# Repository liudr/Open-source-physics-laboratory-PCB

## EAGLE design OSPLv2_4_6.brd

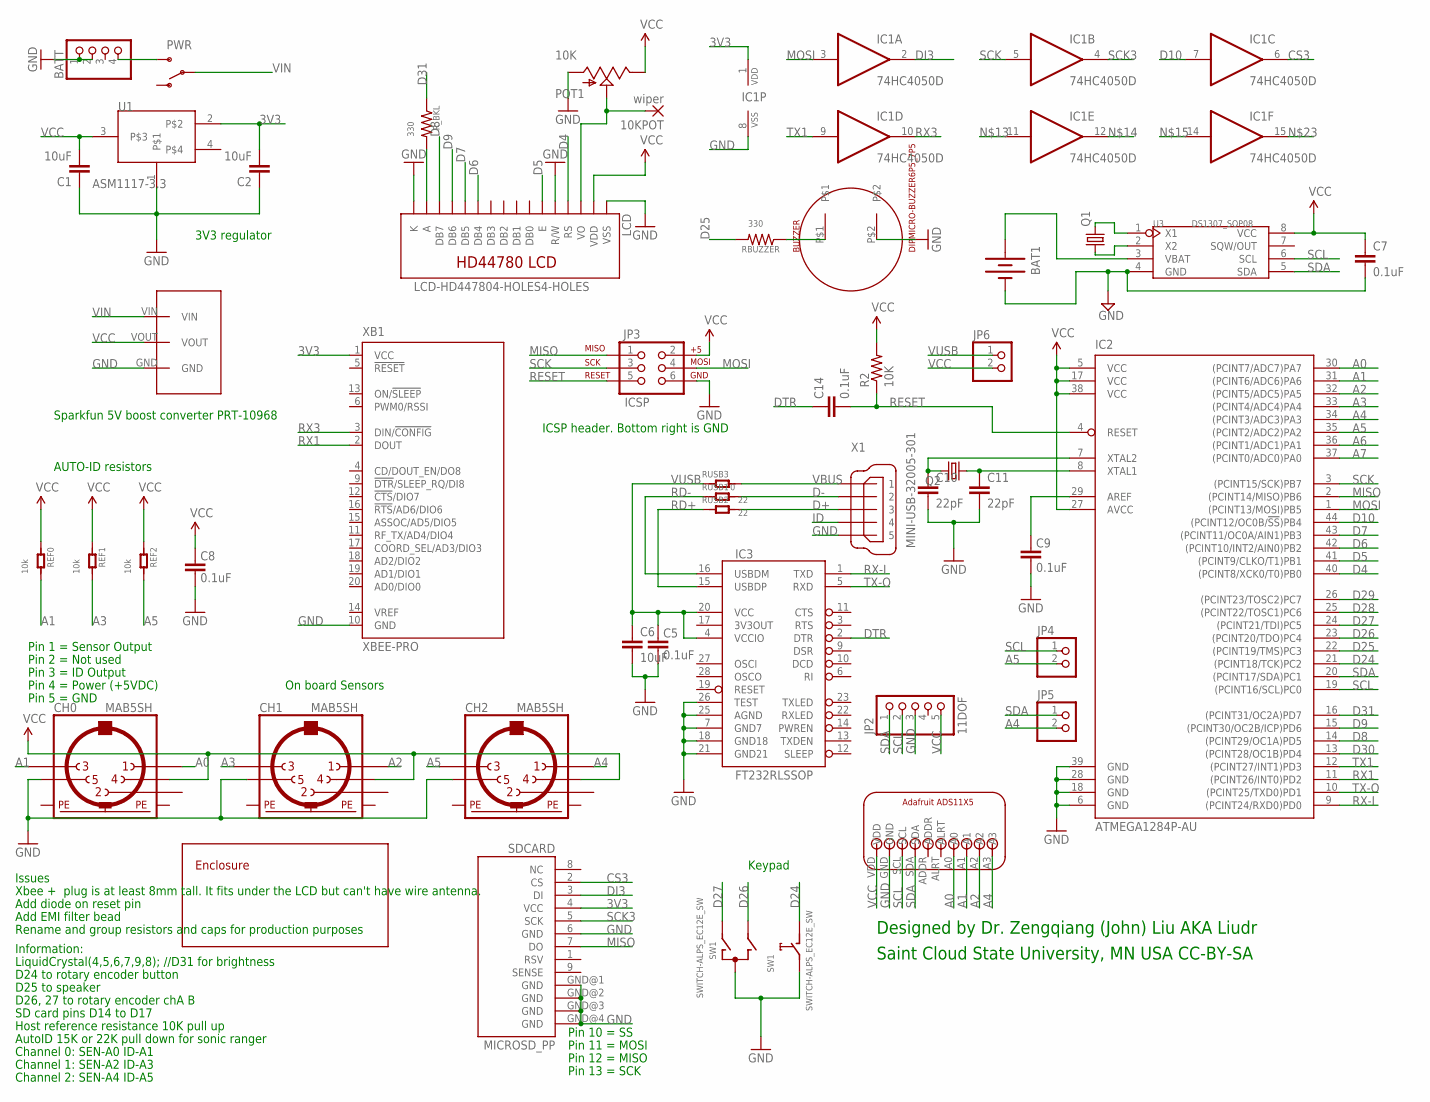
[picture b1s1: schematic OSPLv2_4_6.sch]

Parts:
10KPOT: wiper; 1,6/0,9
BAT1: BATTERYHARWIN12MMHOLDER; HARWIN12MMHOLDER
BATT: PINHD-1X40; 1X04
BUZZER: DIPMICRO-BUZZER6P5_7P5; BUZZER-6P5-7P5
C1, C2, C6: 10uF; 0603-CAP
C5, C7, C8, C9, C14: 0.1uF; 0603-CAP
C10, C11: 22pF; 0603-CAP
CH0, CH1, CH2: MAB5SH
IC1: 74HC4050D; SO16
IC2: ATMEGA1284P-AU; TQFP44
IC3: FT232RLSSOP; SSOP28DB
JP2: 11DOF; 1X05
JP3: ICSP; 2X3
JP4, JP5, JP6: PINHD-1X2SMALL-PADS; 1X02-BIG
LCD: LCD-HD447804-HOLES4-HOLES; LCD-16X2-0HOLES-NO-FRAME
POT1: 10K; 3362U
PWR: SWITCH-SPSTPTH; SWITCH-SPDT
Q1: CRYSTALTC26H; TC26H
Q2: CRYSTALHC49UP; HC49UP
R2: 10K; 0603-RES
RBUZZER: 330; 0603-RES
REF0, REF1, REF2: 10k; R0603
RUSB1, RUSB2: 22; R0603
RUSB3: 0; R0603
R_BKL: 330; 0603-RES
SDCARD: MICROSD_PP
SPEDC-DC: DC-DCBOOSTSPE-DC-DCBOOSTSPE-DC-DC-BOOST; SPE-DC-DC-BOOST
SW1: SWITCH-ALPS_EC12E_SW; SWITCH-ALPS_ALPS_EC12E_SW
U1: ASM1117-3.3; SOT223
U3: DS1307_SOP08; SOP08
U$1: ENCLOSUREAG-54; BUSHING-AG-54
U$2: ADAFRUIT-ADCADS11X5ADS11X5; ADAFRUIT-ADC
X1: MINI-USB-32005-301; 32005-301
XB1: XBEE-PRO

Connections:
3V3: C2.2, IC1.1 (VDD), SDCARD.4 (VCC), U1.2, XB1.1 (VCC)
A0: CH0.1, IC2.30 ((PCINT7/ADC7)PA7), U$2.A0
A1: CH0.3, IC2.31 ((PCINT6/ADC6)PA6), REF0.2, U$2.A1
A2: CH1.1, IC2.32 ((PCINT5/ADC5)PA5), U$2.A2
A3: CH1.3, IC2.33 ((PCINT4/ADC4)PA4), REF1.2
A4: CH2.1, IC2.34 ((PCINT3/ADC3)PA3), JP5.2, U$2.A3
A5: CH2.3, IC2.35 ((PCINT2/ADC2)PA2), JP4.2, REF2.2
A6: IC2.36 ((PCINT1/ADC1)PA1)
A7: IC2.37 ((PCINT0/ADC0)PA0)
AREF1: C9.2, IC2.29 (AREF)
CS3: IC1.6 (O), SDCARD.2 (CS)
D4: IC2.40 ((PCINT8/XCK0/T0)PB0), LCD.RS
D5: IC2.41 ((PCINT9/CLKO/T1)PB1), LCD.E
D6: IC2.42 ((PCINT10/INT2/AIN0)PB2), LCD.DB4
D7: IC2.43 ((PCINT11/OC0A/AIN1)PB3), LCD.DB5
D8: IC2.14 ((PCINT29/OC1A)PD5), LCD.DB7
D9: IC2.15 ((PCINT30/OC2B/ICP)PD6), LCD.DB6
D10: IC1.7 (I), IC2.44 ((PCINT12/OC0B/!SS!)PB4)
D24: IC2.21 ((PCINT18/TCK)PC2), SW1.D (1)
D25: IC2.22 ((PCINT19/TMS)PC3), RBUZZER.2
D26: IC2.23 ((PCINT20/TDO)PC4), SW1.B
D27: IC2.24 ((PCINT21/TDI)PC5), SW1.A
D28: IC2.25 ((PCINT22/TOSC1)PC6)
D29: IC2.26 ((PCINT23/TOSC2)PC7)
D30: IC2.13 ((PCINT28/OC1B)PD4)
D31: IC2.16 ((PCINT31/OC2A)PD7), R_BKL.1
D+: RUSB2.2, X1.3
D-: RUSB1.2, X1.2
DI3: IC1.2 (O), SDCARD.3 (DI)
DTR: C14.1, IC3.2 (DTR)
GND: BAT1.PADGND (-), BATT.1, BATT.2, BUZZER.P$2, C1.1, C2.1, C5.1, C6.2, C7.2, C8.1, C9.1, C10.2, C11.2, CH0.5, CH1.5, CH2.5, IC1.8 (VSS), IC2.6 (GND), IC2.18 (GND), IC2.28 (GND), IC2.39 (GND), IC3.7 (GND7), IC3.18 (GND18), IC3.21 (GND21), IC3.25 (AGND), IC3.26 (TEST), JP2.3, JP3.6, LCD.K, LCD.R/W, LCD.VSS, POT1.P$3 (A), SDCARD.6 (GND), SDCARD.GND@1 (GND), SDCARD.GND@2 (GND), SDCARD.GND@3 (GND), SDCARD.GND@4 (GND), SPEDC-DC.GND, SW1.C, SW1.E (2), U1.1, U3.4 (GND), U$2.GND, X1.5, XB1.10 (GND)
ID: X1.4
MISO: IC2.2 ((PCINT14/MISO)PB6), JP3.1, SDCARD.7 (DO)
MOSI: IC1.3 (I), IC2.1 ((PCINT13/MOSI)PB5), JP3.4
unnamed: C11.1, IC2.8 (XTAL1), Q2.1
unnamed: C10.1, IC2.7 (XTAL2), Q2.2
unnamed: Q1.2, U3.1 (X1)
unnamed: LCD.A, R_BKL.2
unnamed: BATT.4, PWR.3 (S)
unnamed: BAT1.PAD3V3 (+), U3.3 (VBAT)
unnamed: 10KPOT.1, LCD.VO, POT1.P$2 (S)
unnamed: Q1.1, U3.2 (X2)
unnamed: BUZZER.P$1, RBUZZER.1
PE: CH0.PE, CH0.PE@ (PE), CH1.PE, CH1.PE@ (PE), CH2.PE, CH2.PE@ (PE)
RD+: IC3.15 (USBDP), RUSB2.1
RD-: IC3.16 (USBDM), RUSB1.1
RESET: C14.2, IC2.4 (RESET), JP3.5, R2.1
RX1: IC2.11 ((PCINT26/INT0)PD2), XB1.2 (DOUT)
RX3: IC1.10 (O), XB1.3 (DIN/!CONFIG)
RX-I: IC2.9 ((PCINT24/RXD0)PD0), IC3.1 (TXD)
SCK: IC1.5 (I), IC2.3 ((PCINT15/SCK)PB7), JP3.3
SCK3: IC1.4 (O), SDCARD.5 (SCK)
SCL: IC2.19 ((PCINT16/SCL)PC0), JP2.2, JP4.1, U3.6 (SCL), U$2.SCL
SDA: IC2.20 ((PCINT17/SDA)PC1), JP2.1, JP5.1, U3.5 (SDA), U$2.SDA
TX1: IC1.9 (I), IC2.12 ((PCINT27/INT1)PD3)
TX-O: IC2.10 ((PCINT25/TXD0)PD1), IC3.5 (RXD)
VBUS: RUSB3.2, X1.1
VCC: C1.2, C7.1, C8.2, CH0.4, CH1.4, CH2.4, IC2.5 (VCC), IC2.17 (VCC), IC2.27 (AVCC), IC2.38 (VCC), JP2.5, JP3.2, JP6.2, LCD.VDD, POT1.P$1 (E), R2.2, REF0.1, REF1.1, REF2.1, SPEDC-DC.VOUT, U1.3, U3.8 (VCC), U$2.VDD
VIN: PWR.2, SPEDC-DC.VIN
VUSB: C5.2, C6.1, IC3.4 (VCCIO), IC3.20 (VCC), JP6.1, RUSB3.1

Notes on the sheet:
On board Sensors
Keypad
Channel 0: SEN-A0 ID-A1
Channel 1: SEN-A2 ID-A3
Channel 2: SEN-A4 ID-A5
D25 to speaker
Host reference resistance 10K pull up
AutoID 15K or 22K pull down for sonic ranger
Issues
LiquidCrystal(4,5,6,7,9,8); //D31 for brightness
Pin 1 = Sensor Output
Pin 2 = Not used
Pin 3 = ID Output
Pin 4 = Power (+5VDC)
Pin 5 = GND
Information:
SD card pins D14 to D17
3V3 regulator
AUTO-ID resistors
Pin 13 = SCK
Pin 12 = MISO
Pin 11 = MOSI
Pin 10 = SS
D24 to rotary encoder button
Sparkfun 5V boost converter PRT-10968
Add diode on reset pin
ICSP header. Bottom right is GND
Xbee + plug is at least 8mm tall. It fits under the LCD but can't have wire antenna.
D26, 27 to rotary encoder chA B
Add EMI filter bead
Designed by Dr. Zengqiang (John) Liu AKA Liudr
Saint Cloud State University, MN USA CC-BY-SA
Rename and group resistors and caps for production purposes

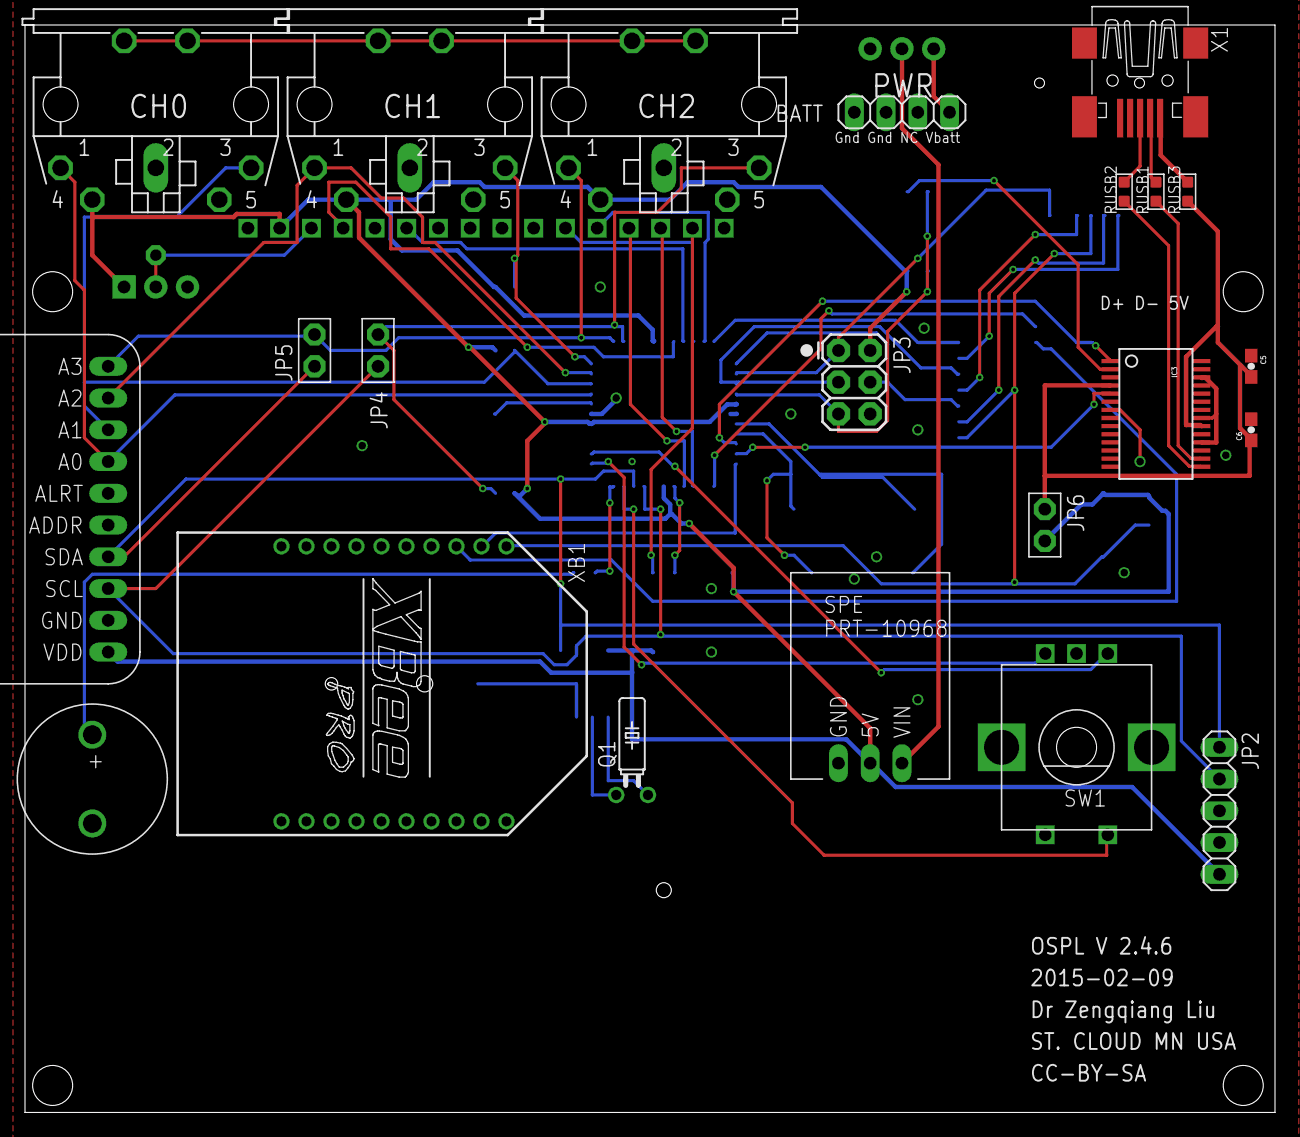
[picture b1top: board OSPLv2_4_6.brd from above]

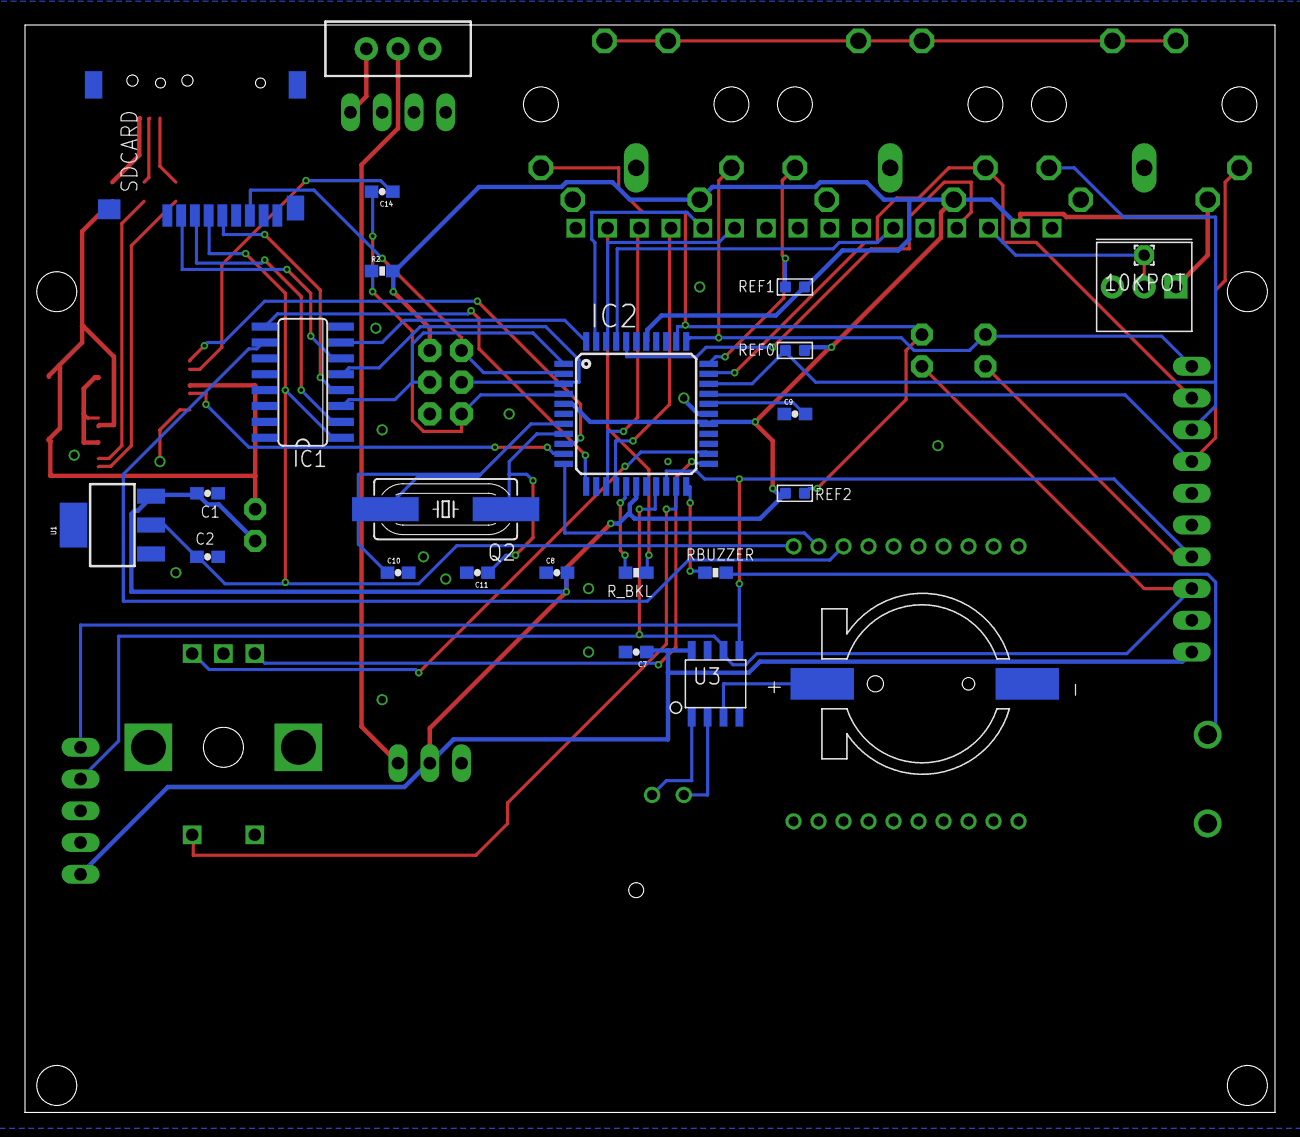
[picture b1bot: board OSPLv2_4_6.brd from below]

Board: 2 copper layers, 100.0 x 87.0 mm, 48 parts (24 on the bottom side), 54 nets.

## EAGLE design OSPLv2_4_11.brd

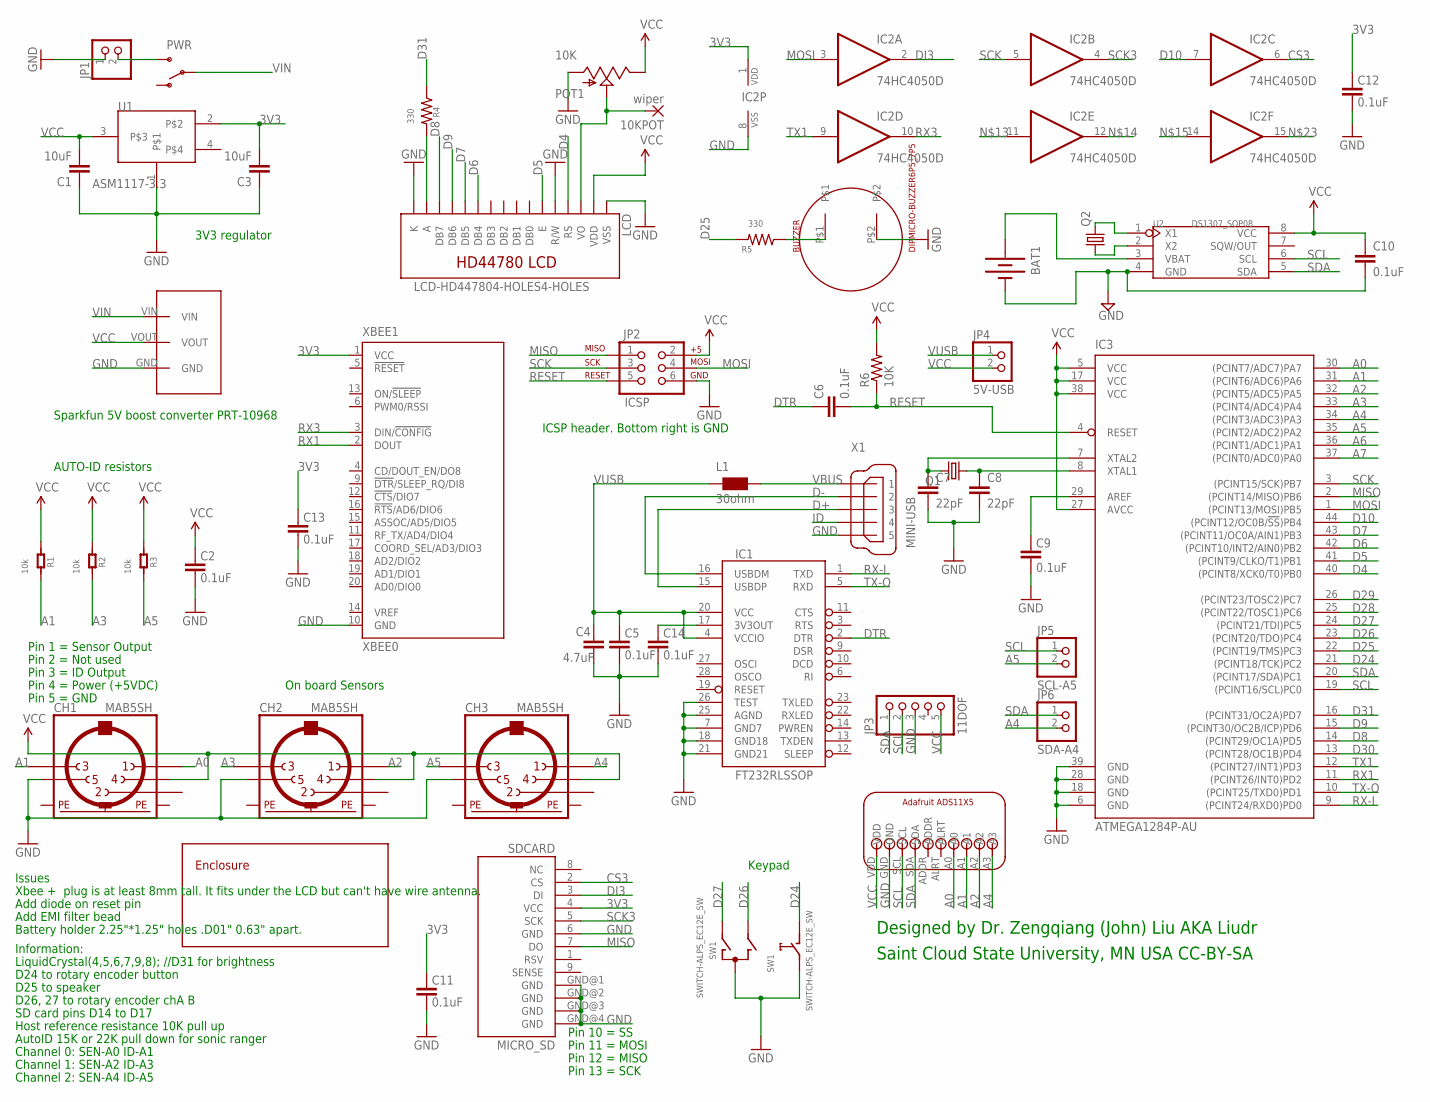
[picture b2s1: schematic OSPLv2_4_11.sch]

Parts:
10KPOT: wiper; 1,6/0,9
BAT1: BATTERYHARWIN12MMHOLDER; HARWIN12MMHOLDER
BUZZER: DIPMICRO-BUZZER6P5_7P5; BUZZER-6P5-7P5
C1, C3: 10uF; 0603-CAP
C2, C5, C6, C9, C10, C11, C12, C13, C14: 0.1uF; 0603-CAP
C4: 4.7uF; 0603-CAP
C7, C8: 22pF; 0603-CAP
CH1, CH2, CH3: MAB5SH
IC1: FT232RLSSOP; SSOP28DB
IC2: 74HC4050D; SO16
IC3: ATMEGA1284P-AU; TQFP44
JP1: PINHD-1X2SMALL-PADS; 1X02-BIG
JP2: ICSP; 2X3
JP3: 11DOF; 1X05
JP4: 5V-USB; 1X02-BIG
JP5: SCL-A5; 1X02-BIG
JP6: SDA-A4; 1X02-BIG
L1: 30ohm; 0805
LCD: LCD-HD447804-HOLES4-HOLES; LCD-16X2-0HOLES-NO-FRAME
POT1: 10K; 3362U
PWR: SWITCH-SPSTPTH; SWITCH-SPDT
Q1: CRYSTALHC49UP; HC49UP
Q2: CRYSTALTC26H; TC26H
R1, R2, R3: 10k; R0603
R4, R5: 330; 0603-RES
R6: 10K; 0603-RES
SDCARD: MICRO_SD; MICROSD_PP
SPEDC-DC: DC-DCBOOSTSPE-DC-DCBOOSTSPE-DC-DC-BOOST; SPE-DC-DC-BOOST
SW1: SWITCH-ALPS_EC12E_SW; SWITCH-ALPS_ALPS_EC12E_SW
U1: ASM1117-3.3; SOT223
U2: DS1307_SOP08; SOP08
U$1: ENCLOSUREAG-54; BUSHING-AG-54
U$2: ADAFRUIT-ADCADS11X5ADS11X5; ADAFRUIT-ADC
X1: MINI-USB; 32005-301
XBEE1: XBEE0; XBEE-PRO

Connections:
3V3: C3.2, C11.2, C12.2, C13.2, IC2.1 (VDD), SDCARD.4 (VCC), U1.2, XBEE1.1 (VCC)
A0: CH1.1, IC3.30 ((PCINT7/ADC7)PA7), U$2.A0
A1: CH1.3, IC3.31 ((PCINT6/ADC6)PA6), R1.2, U$2.A1
A2: CH2.1, IC3.32 ((PCINT5/ADC5)PA5), U$2.A2
A3: CH2.3, IC3.33 ((PCINT4/ADC4)PA4), R2.2
A4: CH3.1, IC3.34 ((PCINT3/ADC3)PA3), JP6.2, U$2.A3
A5: CH3.3, IC3.35 ((PCINT2/ADC2)PA2), JP5.2, R3.2
A6: IC3.36 ((PCINT1/ADC1)PA1)
A7: IC3.37 ((PCINT0/ADC0)PA0)
AREF1: C9.2, IC3.29 (AREF)
CS3: IC2.6 (O), SDCARD.2 (CS)
D4: IC3.40 ((PCINT8/XCK0/T0)PB0), LCD.RS
D5: IC3.41 ((PCINT9/CLKO/T1)PB1), LCD.E
D6: IC3.42 ((PCINT10/INT2/AIN0)PB2), LCD.DB4
D7: IC3.43 ((PCINT11/OC0A/AIN1)PB3), LCD.DB5
D8: IC3.14 ((PCINT29/OC1A)PD5), LCD.DB7
D9: IC3.15 ((PCINT30/OC2B/ICP)PD6), LCD.DB6
D10: IC2.7 (I), IC3.44 ((PCINT12/OC0B/!SS!)PB4)
D24: IC3.21 ((PCINT18/TCK)PC2), SW1.D (1)
D25: IC3.22 ((PCINT19/TMS)PC3), R5.2
D26: IC3.23 ((PCINT20/TDO)PC4), SW1.B
D27: IC3.24 ((PCINT21/TDI)PC5), SW1.A
D28: IC3.25 ((PCINT22/TOSC1)PC6)
D29: IC3.26 ((PCINT23/TOSC2)PC7)
D30: IC3.13 ((PCINT28/OC1B)PD4)
D31: IC3.16 ((PCINT31/OC2A)PD7), R4.1
D+: IC1.15 (USBDP), X1.3
D-: IC1.16 (USBDM), X1.2
DI3: IC2.2 (O), SDCARD.3 (DI)
DTR: C6.1, IC1.2 (DTR)
GND: BAT1.PADGND (-), BUZZER.P$2, C1.1, C2.1, C3.1, C4.2, C5.1, C7.2, C8.2, C9.1, C10.2, C11.1, C12.1, C13.1, C14.1, CH1.5, CH2.5, CH3.5, IC1.7 (GND7), IC1.18 (GND18), IC1.21 (GND21), IC1.25 (AGND), IC1.26 (TEST), IC2.8 (VSS), IC3.6 (GND), IC3.18 (GND), IC3.28 (GND), IC3.39 (GND), JP1.1, JP2.6, JP3.3, LCD.K, LCD.R/W, LCD.VSS, POT1.P$3 (A), SDCARD.6 (GND), SDCARD.GND@1 (GND), SDCARD.GND@2 (GND), SDCARD.GND@3 (GND), SDCARD.GND@4 (GND), SPEDC-DC.GND, SW1.C, SW1.E (2), U1.1, U2.4 (GND), U$2.GND, X1.5, XBEE1.10 (GND)
ID: X1.4
MISO: IC3.2 ((PCINT14/MISO)PB6), JP2.1, SDCARD.7 (DO)
MOSI: IC2.3 (I), IC3.1 ((PCINT13/MOSI)PB5), JP2.4
unnamed: C8.1, IC3.8 (XTAL1), Q1.1
unnamed: C7.1, IC3.7 (XTAL2), Q1.2
unnamed: Q2.2, U2.1 (X1)
unnamed: LCD.A, R4.2
unnamed: JP1.2, PWR.3 (S)
unnamed: BAT1.PAD3V3 (+), U2.3 (VBAT)
unnamed: 10KPOT.1, LCD.VO, POT1.P$2 (S)
unnamed: Q2.1, U2.2 (X2)
unnamed: C14.2, IC1.17 (3V3OUT)
unnamed: BUZZER.P$1, R5.1
PE: CH1.PE, CH1.PE@ (PE), CH2.PE, CH2.PE@ (PE), CH3.PE, CH3.PE@ (PE)
RESET: C6.2, IC3.4 (RESET), JP2.5, R6.1
RX1: IC3.11 ((PCINT26/INT0)PD2), XBEE1.2 (DOUT)
RX3: IC2.10 (O), XBEE1.3 (DIN/!CONFIG)
RX-I: IC1.1 (TXD), IC3.9 ((PCINT24/RXD0)PD0)
SCK: IC2.5 (I), IC3.3 ((PCINT15/SCK)PB7), JP2.3
SCK3: IC2.4 (O), SDCARD.5 (SCK)
SCL: IC3.19 ((PCINT16/SCL)PC0), JP3.2, JP5.1, U2.6 (SCL), U$2.SCL
SDA: IC3.20 ((PCINT17/SDA)PC1), JP3.1, JP6.1, U2.5 (SDA), U$2.SDA
TX1: IC2.9 (I), IC3.12 ((PCINT27/INT1)PD3)
TX-O: IC1.5 (RXD), IC3.10 ((PCINT25/TXD0)PD1)
VBUS: L1.2, X1.1
VCC: C1.2, C2.2, C10.1, CH1.4, CH2.4, CH3.4, IC3.5 (VCC), IC3.17 (VCC), IC3.27 (AVCC), IC3.38 (VCC), JP2.2, JP3.5, JP4.2, LCD.VDD, POT1.P$1 (E), R1.1, R2.1, R3.1, R6.2, SPEDC-DC.VOUT, U1.3, U2.8 (VCC), U$2.VDD
VIN: PWR.2, SPEDC-DC.VIN
VUSB: C4.1, C5.2, IC1.4 (VCCIO), IC1.20 (VCC), JP4.1, L1.1

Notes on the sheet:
On board Sensors
Keypad
Channel 0: SEN-A0 ID-A1
Channel 1: SEN-A2 ID-A3
Channel 2: SEN-A4 ID-A5
D25 to speaker
Host reference resistance 10K pull up
AutoID 15K or 22K pull down for sonic ranger
Issues
LiquidCrystal(4,5,6,7,9,8); //D31 for brightness
Pin 1 = Sensor Output
Pin 2 = Not used
Pin 3 = ID Output
Pin 4 = Power (+5VDC)
Pin 5 = GND
Information:
SD card pins D14 to D17
3V3 regulator
AUTO-ID resistors
Pin 13 = SCK
Pin 12 = MISO
Pin 11 = MOSI
Pin 10 = SS
D24 to rotary encoder button
Sparkfun 5V boost converter PRT-10968
Add diode on reset pin
ICSP header. Bottom right is GND
Xbee + plug is at least 8mm tall. It fits under the LCD but can't have wire antenna.
D26, 27 to rotary encoder chA B
Add EMI filter bead
Designed by Dr. Zengqiang (John) Liu AKA Liudr
Saint Cloud State University, MN USA CC-BY-SA
Battery holder 2.25"*1.25" holes .D01" 0.63" apart.

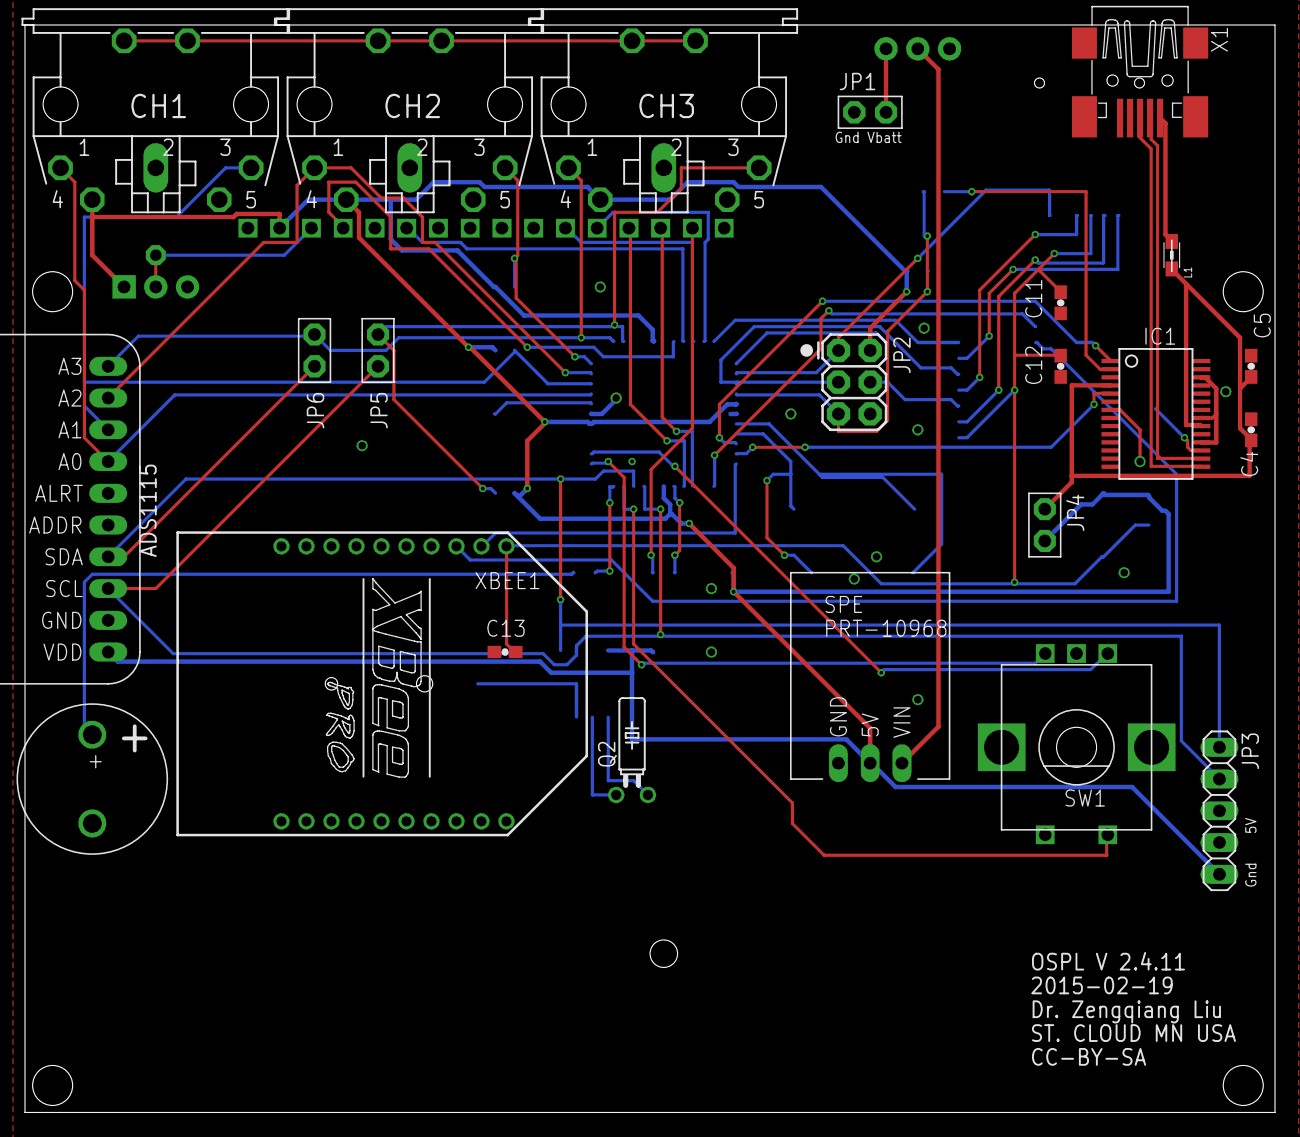
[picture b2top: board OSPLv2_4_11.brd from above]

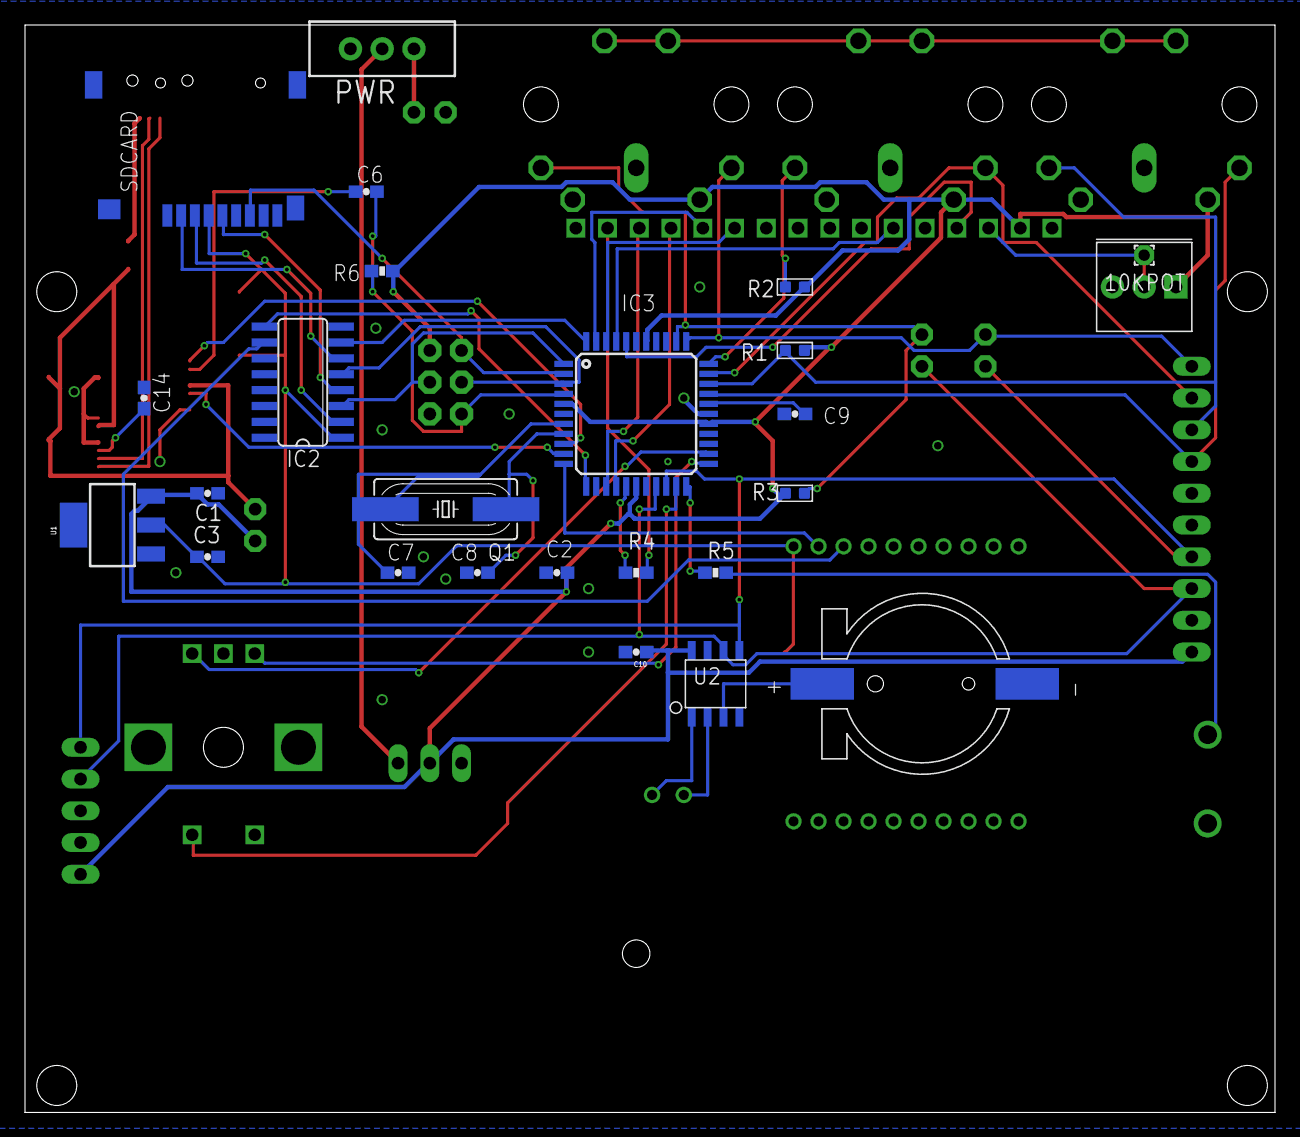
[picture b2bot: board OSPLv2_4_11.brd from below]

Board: 2 copper layers, 100.0 x 87.0 mm, 50 parts (25 on the bottom side), 53 nets.
